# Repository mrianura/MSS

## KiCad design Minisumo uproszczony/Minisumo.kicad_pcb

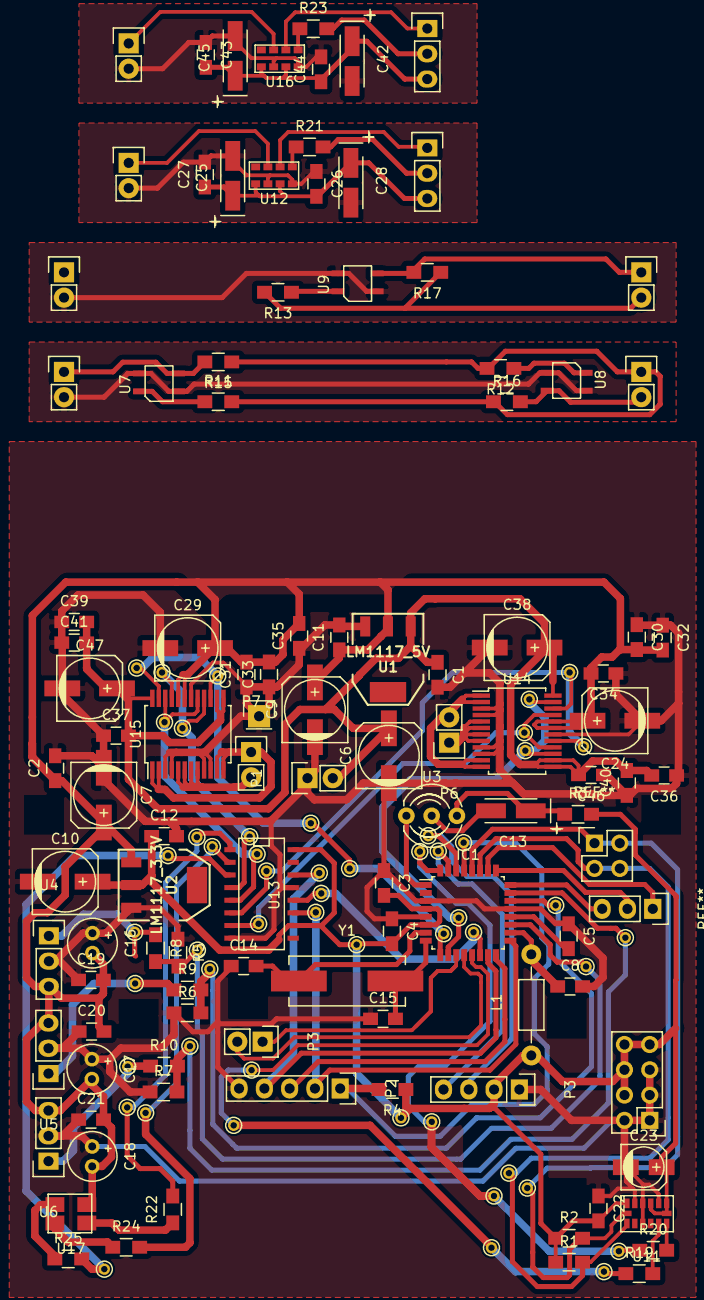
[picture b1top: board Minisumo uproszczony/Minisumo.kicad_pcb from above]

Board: 2 copper layers, 95 parts (0 on the bottom side), 56 nets.

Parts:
C1, C2, C3, C4, C5, C8, C11, C12, C19, C20, C21, C22, C26, C27, C30, C31, C32, C33, C34, C35, C36, C37, C39, C40, C41, C43, C44, C46: 100nF; C_0805_HandSoldering
C6, C7, C9, C10, C24, C29, C38, C47: 100uF; c_elec_6.3x7.7
C13, C25, C42: 4.7uF; TantalC_SizeA_EIA-3216_HandSoldering
C14, C15: 22pF; C_0805_HandSoldering
C16, C17, C18: 1uF; Elko_vert_11x5mm_RM2
C23: 22uF; c_elec_4x4.5
C28, C45: 1uF; TantalC_SizeA_EIA-3216_HandSoldering
IC1: ATMEGA328P-A; LQFP-32_7x7mm_Pitch0.8mm
L1: 100mH; Resistor_Horizontal_RM10mm
P1: bateria; Pin_Header_Straight_1x02
P2: PROGRAMATOR; Pin_Header_Straight_1x05
P3: CONN_01X04; Pin_Header_Straight_1x02
P3#2: CONN_01X04; Pin_Header_Straight_1x04
P6: silnik2; Pin_Header_Straight_1x02
P7: silnik1; Pin_Header_Straight_1x02
R1, R2, R4: 10K; R_0805_HandSoldering
R3: 330; R_0805_HandSoldering
R5, R6, R7: 22K; R_0805_HandSoldering
R8, R9, R10: 6K8; R_0805_HandSoldering
R11, R12, R13: 100; R_0805_HandSoldering
R15, R16, R17: 10k; R_0805_HandSoldering
R19, R20, R21, R23: 1k; R_0805_HandSoldering
R22, R24, R25: 220; R_0805_HandSoldering
U1: LM1117_5V; SOT223
U2: LM1117_3.3V; SOT223
U3: TSOP4838; LED-5MM-3
U4, U5, U6: SHARP_10-80; Pin_Header_Straight_1x03
U7, U8, U9: KTIR0711S
U11: MMA7455L; LGA_14
U12, U16: SFH7773; sfh7773
U13: 74HC595; SO-16-N
U14, U15: TB6612
U17: RGB_diode; RGB_C_Anode
Y1: 16mHz; Crystal_HC49-SD_SMD

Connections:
+3V3: C3.2, C4.2, C10.1, C12.1, C22.2, C23.1, C25.1, C26.2, C27.1, C28.1, C42.1, C43.2, C44.1, C45.1, IC1.4, IC1.6, L1.1, P3#2.2, R1.1, R2.1, R3.2, R4.1, R11.2, R12.2, R13.2, R15.1, R16.1, R17.1, U2.2, U11.1, U11.4, U11.6, U11.7, U12.1, U12.3, U13.10, U13.16, U16.1, U16.3
+5V: C2.1, C7.1, C9.1, C11.1, C16.2, C17.2, C18.2, C19.2, C20.2, C21.2, C24.1, C29.1, C30.2, C31.2, C32.2, C33.2, C34.2, C35.2, U1.2, U2.1, U4.3, U5.3, U6.3, U14.19, U14.20, U15.19, U15.20, U17.2
/ACC_DRDY: IC1.32, R20.1
/ACC_INT2: IC1.13, R19.1
/AIN_1: U13.5, U15.17, U15.22
/AIN_2: U13.4, U15.16, U15.21
/BIN_1: U13.6, U14.17, U14.22
/BIN_2: U13.7, U14.16, U14.21
/INT_10_1: IC1.12, P3.2, R23.2
/INT_10_2: IC1.11, P3.1, R21.2
/KILL: IC1.30, P3#2.3
/KTIR_(1): IC1.24, R15.2, U7.4
/KTIR_(2): IC1.25, R16.2, U8.4
/KTIR_(3): IC1.26, R17.2, U9.4
/MISO: IC1.16, P2.3
/MOSI: IC1.15, P2.4, U13.14
/PWM_A: IC1.9, U15.15, U15.23
/PWM_B: IC1.10, U14.15, U14.23
/RST_328: IC1.29, P2.1, R4.2
/SCK: IC1.17, P2.2, U13.11
/SCL: IC1.28, R2.2, U11.14, U12.6, U16.6
/SDA: IC1.27, R1.2, U11.13, U12.7, U16.7
/SHARP_1: IC1.19, R5.2, R8.2
/SHARP_2: IC1.22, R6.2, R9.2
/SHARP_3: IC1.23, R7.2, R10.2
/SS: IC1.14, U13.12
/START: IC1.31, P3#2.4
/S_A_1: P7.1, U15.1, U15.2, U15.11, U15.12
/S_A_2: P7.2, U15.5, U15.6, U15.7, U15.8
/S_B_1: P6.2, U14.1, U14.2, U14.11, U14.12
/S_B_2: P6.1, U14.5, U14.6, U14.7, U14.8
/XTAL1: C14.2, IC1.7, Y1.1
/XTAL2: C15.2, IC1.8, Y1.2
GND: C1.2, C2.2, C3.1, C4.1, C5.1, C6.2, C7.2, C8.2, C9.2, C10.2, C11.2, C12.2, C14.1, C15.1, C16.1, C17.1, C18.1, C19.1, C20.1, C21.1, C22.1, C23.2, C24.2, C25.2, C26.1, C27.2, C28.2, C29.2, C30.1, C31.1, C32.1, C33.1, C34.1, C35.1, C36.1, C37.1, C38.2, C39.1, C40.1, C41.1, C42.2, C43.1, C44.2, C45.2, C46.1, C47.2, IC1.3, IC1.5, IC1.21, P1.1, P2.5, P3#2.1, R5.1, R6.1, R7.1, U1.3, U2.3, U4.2, U5.2, U6.2, U7.2, U7.3, U8.2, U8.3, U9.2, U9.3, U11.2, U11.3, U11.5, U11.11, U12.2, U12.4, U13.8, U13.13, U14.3, U14.4, U14.9, U14.10, U14.18, U15.3, U15.4, U15.9, U15.10, U15.18, U16.2, U16.4
unnamed: C5.2, IC1.20
unnamed: C8.1, IC1.18, L1.2
unnamed: C13.1, R3.1, U3.3
unnamed: C13.2, U3.2
unnamed: IC1.1, U3.1
unnamed: R8.1, U4.1
unnamed: R9.1, U5.1
unnamed: R10.1, U6.1
unnamed: R11.1, U7.1
unnamed: R12.1, U8.1
unnamed: R13.1, U9.1
unnamed: R19.2, U11.9
unnamed: R20.2, U11.8
unnamed: R21.1, U12.5
unnamed: R22.1, U17.4
unnamed: R22.2, U13.1
unnamed: R23.1, U16.5
unnamed: R24.1, U17.3
unnamed: R24.2, U13.2
unnamed: R25.1, U17.1
unnamed: R25.2, U13.3
VCC: C1.1, C6.1, C36.2, C37.2, C38.1, C39.2, C40.2, C41.2, C46.2, C47.1, P1.2, U1.1, U14.13, U14.14, U14.24, U15.13, U15.14, U15.24

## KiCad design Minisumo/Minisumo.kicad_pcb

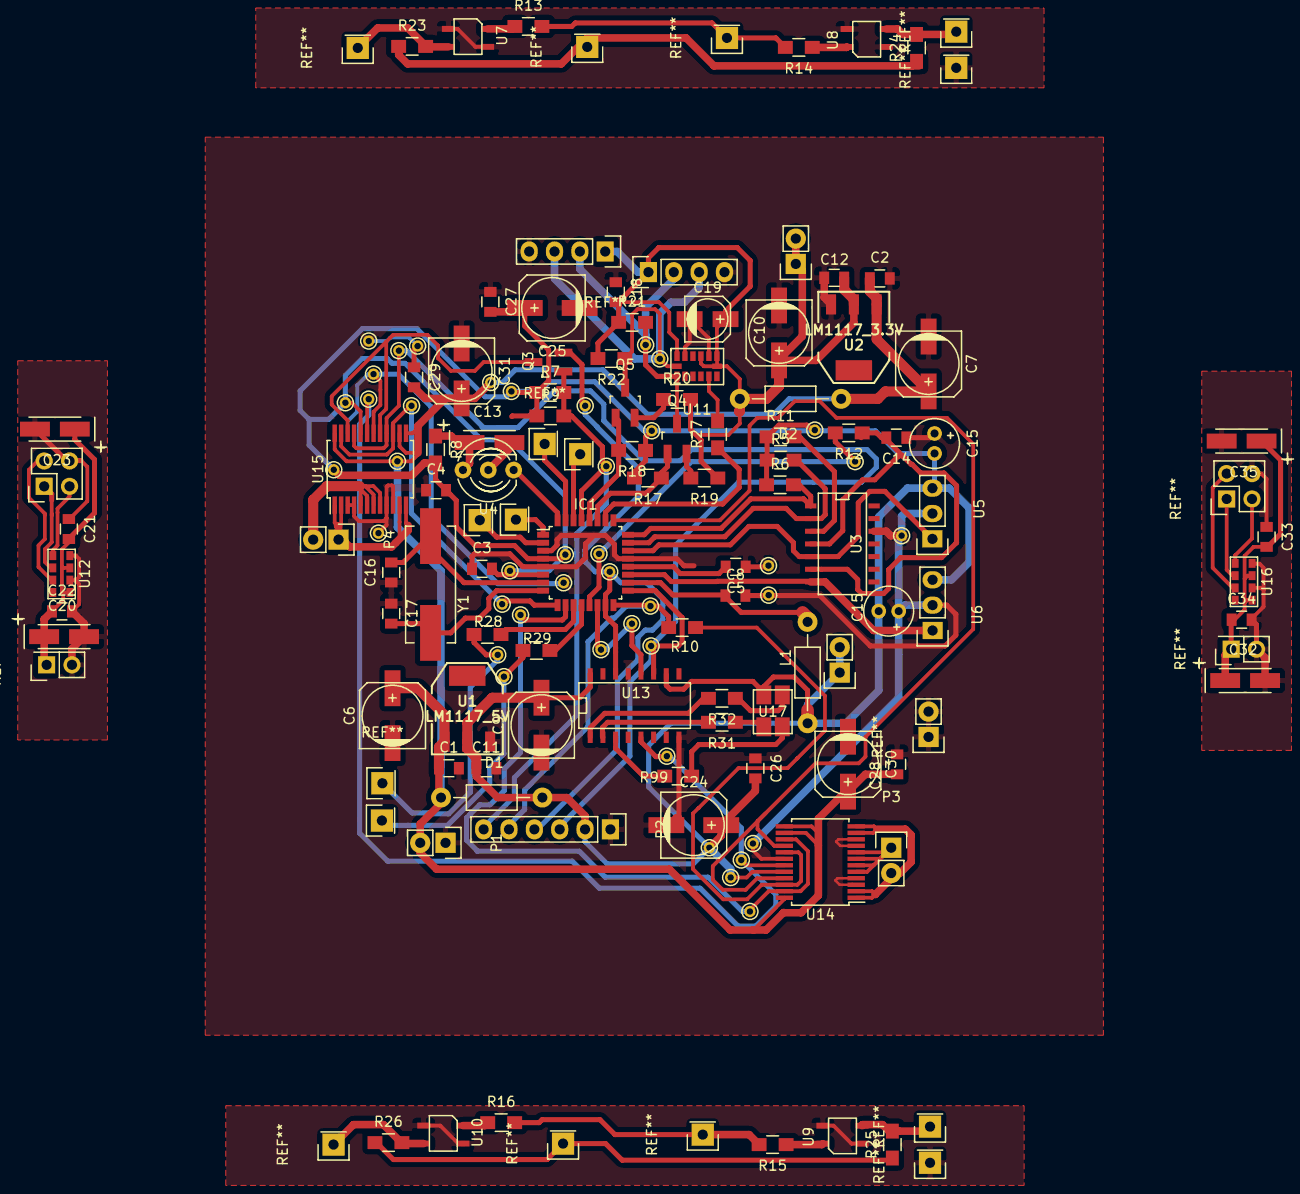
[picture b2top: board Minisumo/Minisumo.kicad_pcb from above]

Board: 2 copper layers, 93 parts (0 on the bottom side), 59 nets.

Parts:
C1, C2, C3, C4, C5, C8, C11, C12, C14, C18, C21, C22, C26, C27, C28, C29, C33, C34: 100nF; C_0805
C6, C7, C9, C10, C24, C25, C30, C31: 100uF; c_elec_6.3x7.7
C13, C20, C32: 4.7uF; TantalC_SizeA_EIA-3216_HandSoldering
C15, C15#2: 1uF; Elko_vert_11x5mm_RM2
C16, C17: 22pF; C_0805
C19: 22uF; c_elec_4x4.5
C23, C35: 1uF; TantalC_SizeA_EIA-3216_HandSoldering
D1, D2: D_Schottky; Resistor_Horizontal_RM10mm
IC1: ATMEGA328P-A; LQFP-32_7x7mm_Pitch0.8mm
L1: 100mH; Resistor_Horizontal_RM10mm
P1: bateria; Pin_Header_Straight_1x02
P2: PROGRAMATOR; Pin_Header_Straight_1x06
P3: silnik2; Pin_Header_Straight_1x02
P4: silnik1; Pin_Header_Straight_1x02
Q3: BC817-25; SOT-23_Handsoldering
Q4, Q5: BSS138; SOT-23_Handsoldering
R5, R6: 47k; R_0805_HandSoldering
R7, R10, R23, R24, R25, R26: 10k; R_0805_HandSoldering
R8: 330; R_0805_HandSoldering
R9: 10K; R_0805_HandSoldering
R11: 3k; R_0805_HandSoldering
R12: 33k; R_0805_HandSoldering
R13, R14, R15, R16: 100; R_0805_HandSoldering
R17, R18, R19, R20, R21, R22: 4,7k; R_0805_HandSoldering
R27, R28, R29: 1k; R_0805_HandSoldering
R31, R32, R99: 220; R_0805_HandSoldering
U1: LM1117_5V; SOT223
U2: LM1117_3.3V; SOT223
U3: LM339; SOIC-14_N
U4: IR; LED-5MM-3
U5: Socket_Strip_Straight_1x03
U6: SHARP_10-80; Socket_Strip_Straight_1x03
U7, U8, U9, U10: KTIR0711S
U11: MMA7455L; LGA_14
U12, U16: SFH7773; sfh7773
U13: 74HC595; SO-16-N
U14, U15: TB6612
U17: RGB; RGB_C_Anode
Y1: 16mHz; Crystal_HC49-SD_SMD

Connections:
+3V3: C10.1, C12.1, C18.2, C19.1, C20.1, C21.2, C22.1, C23.1, C32.1, C33.2, C34.1, C35.1, D2.2, R13.2, R14.2, R15.2, R16.2, R19.1, R20.2, R21.1, R22.2, U2.2, U11.1, U11.4, U11.6, U11.7, U12.1, U12.3, U16.1, U16.3
+5V: C3.2, C4.2, C9.1, C11.1, C15.2, C15#2.2, C24.1, C25.1, C26.2, C27.2, D1.2, IC1.4, IC1.6, L1.1, P2.2, R5.1, R6.1, R7.1, R8.2, R9.1, R11.1, R17.2, R18.1, R23.1, R24.1, R25.1, R26.1, U1.2, U5.3, U6.3, U13.10, U13.16, U14.20, U15.20, U17.2
/ACC_INT2: IC1.26, R27.1
/AIN_1: Q3.3, U15.17, U15.22
/AIN_2: IC1.17, P2.3, U13.11, U15.16, U15.21
/BIN_1: R10.1, U14.17, U14.22
/BIN_2: IC1.25, U14.16, U14.21
/INT_10_1: IC1.12, R29.2
/INT_10_2: IC1.11, R28.2
/MISO_328: IC1.16, P2.5, R10.2
/MOSI_328: IC1.15, P2.4, Q3.2, U13.14
/PCINT16_(1): IC1.30, R23.2, U7.4
/PCINT17_(2): IC1.31, R24.2, U8.4
/PCINT20_(3): IC1.2, R25.2, U9.4
/PCINT21_(4): IC1.1, R26.2, U10.4
/PWM_A: IC1.9, U15.15, U15.23
/PWM_B: IC1.10, U14.15, U14.23
/PWM_SHARP: IC1.13, R12.2
/RST_328: IC1.29, P2.6, Q3.1, R7.2, R9.2
/SCL: IC1.28, Q5.1, R18.2
/SCL_3.3: Q5.3, R22.1, U11.14, U12.6, U16.6
/SDA: IC1.27, Q4.1, R17.1
/SDA_3.3: Q4.3, R21.2, U11.13, U12.7, U16.7
/SHARP1_INT: IC1.24, R6.2, U3.1
/SHARP2_INT: IC1.23, R5.2, U3.2
/SHARP_1: IC1.19, U3.7, U6.1
/SHARP_2: IC1.22, U3.5, U5.1
/SHARP_POZ: C14.2, R12.1, U3.4, U3.6
/STBY_ON: U13.5, U14.19, U15.19
/S_A_1: P4.1, U15.1, U15.2, U15.11, U15.12
/S_A_2: P4.2, U15.5, U15.6, U15.7, U15.8
/S_B_1: P3.2, U14.1, U14.2, U14.11, U14.12
/S_B_2: P3.1, U14.5, U14.6, U14.7, U14.8
/XTAL1: C16.2, IC1.7, Y1.1
/XTAL2: C17.2, IC1.8, Y1.2
GND: C1.2, C2.2, C3.1, C4.1, C5.1, C6.2, C7.2, C8.2, C9.2, C10.2, C11.2, C12.2, C14.1, C15.1, C15#2.1, C16.1, C17.1, C18.1, C19.2, C20.2, C21.1, C22.2, C23.2, C24.2, C25.2, C26.1, C27.1, C28.1, C29.1, C30.2, C31.2, C32.2, C33.1, C34.2, C35.2, IC1.3, IC1.5, IC1.21, P1.1, P2.1, U1.3, U2.3, U3.12, U5.2, U6.2, U7.2, U7.3, U8.2, U8.3, U9.2, U9.3, U10.2, U10.3, U11.2, U11.5, U12.2, U12.4, U13.8, U13.13, U14.3, U14.4, U14.9, U14.10, U14.18, U15.3, U15.4, U15.9, U15.10, U15.18, U16.2, U16.4
unnamed: C5.2, IC1.20
unnamed: C8.1, IC1.18, L1.2
unnamed: C13.1, R8.1, U4.3
unnamed: C13.2, U4.2
unnamed: IC1.14, U13.12
unnamed: IC1.32, U4.1
unnamed: Q4.2, R19.2
unnamed: Q5.2, R20.1
unnamed: R11.2, U3.3
unnamed: R13.1, U7.1
unnamed: R14.1, U8.1
unnamed: R15.1, U9.1
unnamed: R16.1, U10.1
unnamed: R27.2, U11.9
unnamed: R28.1, U12.5
unnamed: R29.1, U16.5
unnamed: R31.1, U17.1
unnamed: R31.2, U13.2
unnamed: R32.1, U17.4
unnamed: R32.2, U13.1
unnamed: R99.1, U17.3
unnamed: R99.2, U13.3
VCC: C1.1, C2.1, C6.1, C7.1, C28.2, C29.2, C30.1, C31.1, D1.1, D2.1, P1.2, U1.1, U2.1, U14.13, U14.14, U14.24, U15.13, U15.14, U15.24

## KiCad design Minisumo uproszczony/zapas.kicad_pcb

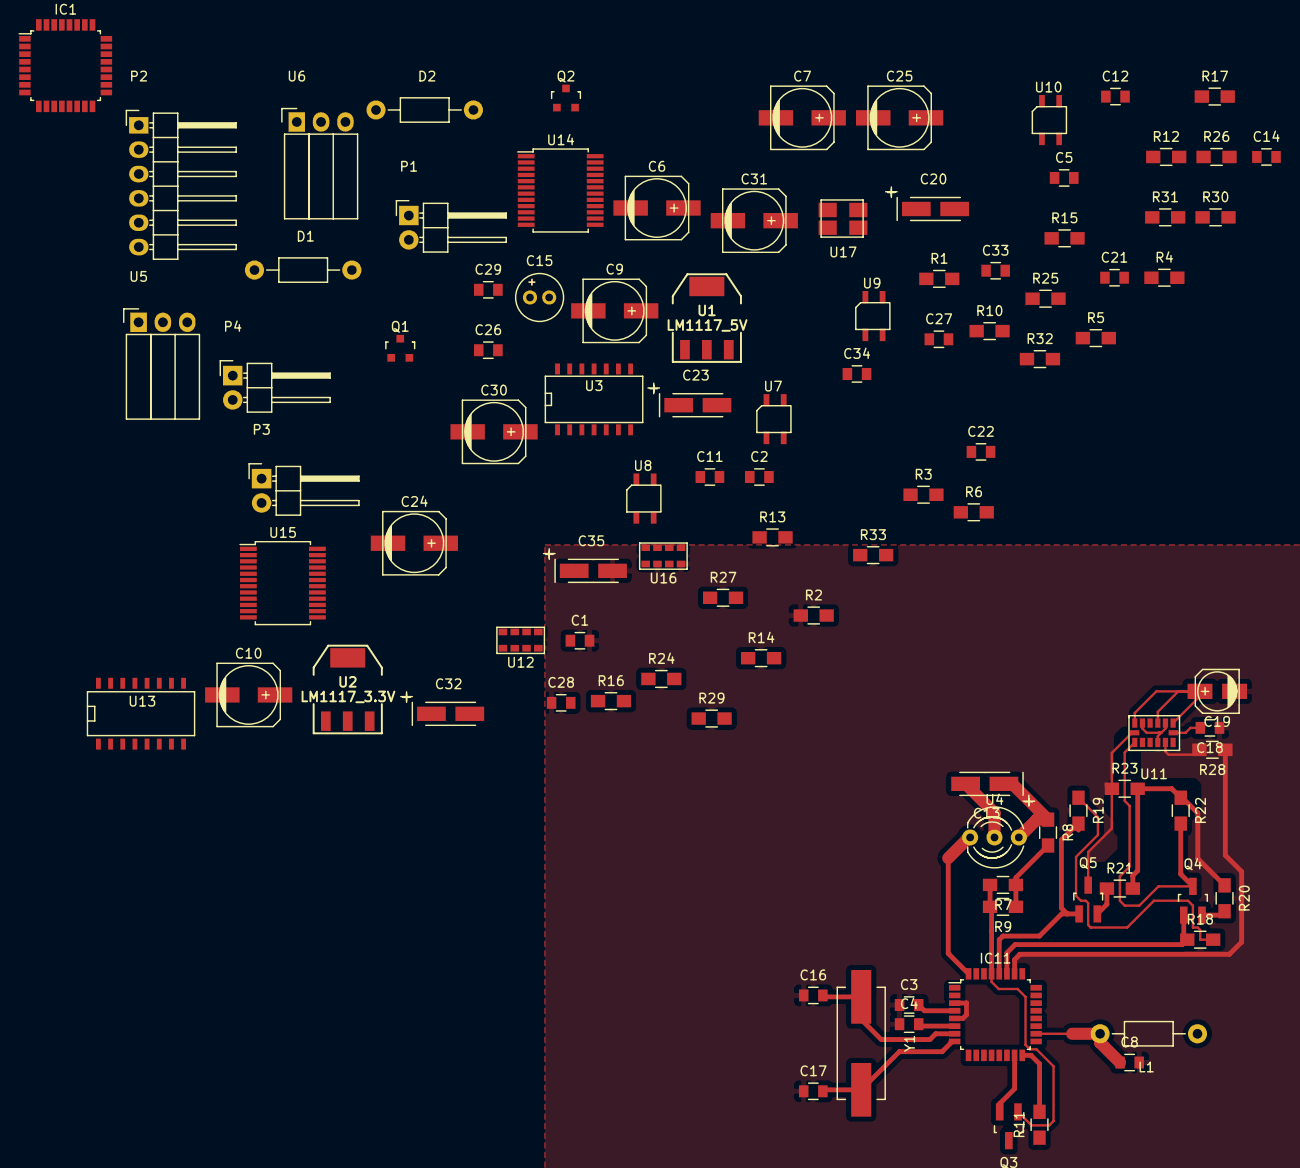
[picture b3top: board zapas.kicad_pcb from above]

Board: 2 copper layers, 100 parts (0 on the bottom side), 64 nets.

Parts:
C1, C2, C3, C4, C5, C8, C11, C12, C14, C18, C21, C22, C26, C27, C28, C29, C33, C34: 100nF; C_0805
C6, C7, C9, C10, C24, C25, C30, C31: 100uF; c_elec_6.3x7.7
C13, C20, C32: 4.7uF; TantalC_SizeA_EIA-3216_HandSoldering
C15: 1uF; Elko_vert_11x5mm_RM2
C16, C17: 22pF; C_0805
C19: 22uF; c_elec_4x4.5
C23, C35: 1uF; TantalC_SizeA_EIA-3216_HandSoldering
D1, D2: D_Schottky; Resistor_Horizontal_RM10mm
IC1, IC11: ATMEGA328P-A; LQFP-32_7x7mm_Pitch0.8mm
L1: 100mH; Resistor_Horizontal_RM10mm
P1: bateria; Pin_Header_Angled_1x02
P2: PROGRAMATOR; Pin_Header_Angled_1x06
P3: silnik2; Pin_Header_Angled_1x02
P4: silnik1; Pin_Header_Angled_1x02
Q1, Q2: IRLML2246TRPBF; SOT-23
Q3: BC817-25; SOT-23_Handsoldering
Q4, Q5: BSS138; SOT-23_Handsoldering
R1, R2, R5, R6: 47k; R_0805_HandSoldering
R3, R4, R28, R29, R30: 1k; R_0805_HandSoldering
R7, R11, R24, R25, R26, R27: 10k; R_0805_HandSoldering
R8: 330; R_0805_HandSoldering
R9: 10K; R_0805_HandSoldering
R10, R12: 3k; R_0805_HandSoldering
R13: 33k; R_0805_HandSoldering
R14, R15, R16, R17: 100; R_0805_HandSoldering
R18, R19, R20, R21, R22, R23: 4,7k; R_0805_HandSoldering
R31, R32, R33: 220; R_0805_HandSoldering
U1: LM1117_5V; SOT223
U2: LM1117_3.3V; SOT223
U3: LM339; SOIC-14_N
U4: TSOP4836; LED-5MM-3
U5, U6: SHARP_10-80; Socket_Strip_Angled_1x03
U7, U8, U9, U10: KTIR0711S
U11: MMA7455L; LGA_14
U12, U16: SFH7773; sfh7773
U13: 74HC595; SO-16-N
U14, U15: TB6612
U17: RGB_diode; RGB_C_Anode
Y1: 16mHz; Crystal_HC49-SD_SMD

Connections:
+3V3: C18.2, C19.1, C20.1, C21.2, C22.1, C23.1, C32.1, C33.2, C34.1, C35.1, Q2.2, R14.2, R15.2, R16.2, R17.2, R20.1, R21.2, R22.1, R23.2, U11.1, U11.4, U11.6, U11.7, U12.1, U12.3, U16.1, U16.3
+5V: C15.2, C24.1, C25.1, C26.2, C27.2, Q1.2, R5.1, R6.1, R10.1, R12.1, R18.2, R19.1, R24.1, R25.1, R26.1, R27.1, U5.3, U6.3, U14.20, U15.20
+5VA: C3.2, C4.2, C9.1, C11.1, D1.2, IC1.4, IC1.6, IC11.4, IC11.6, L1.1, P2.6, Q1.3, R7.1, R8.2, R9.1, U1.2, U13.10, U17.2
/ACC_INT2: IC1.26, IC11.26, R28.1
/AIN_1: Q3.3, U15.17, U15.22
/AIN_2: IC1.17, IC11.17, P2.3, U13.11, U15.16, U15.21
/BIN_1: R11.1, U14.17, U14.22
/BIN_2: IC1.25, IC11.25, U14.16, U14.21
/INT_10_1: IC1.12, IC11.12, R30.2
/INT_10_2: IC1.1, IC11.1, R29.2
/MISO_328: IC1.16, IC11.16, P2.1, R11.2
/MOSI_328: IC1.15, IC11.15, P2.2, Q3.2, U13.14
/PCINT16_(1): IC1.30, IC11.30, R24.2, U7.4
/PCINT17_(2): IC1.31, IC11.31, R25.2, U8.4
/PCINT20_(3): IC1.2, IC11.2, R26.2, U9.4
/PCINT21_(4): IC1.11, IC11.11, R27.2, U10.4
/PWM_A: IC1.9, IC11.9, U15.15, U15.23
/PWM_B: IC1.10, IC11.10, U14.15, U14.23
/PWM_SHARP: IC1.13, IC11.13, R13.2
/RST_328: IC1.29, IC11.29, P2.4, Q3.1, R7.2, R9.2
/SCL: IC1.28, IC11.28, Q5.1, R19.2
/SCL_3.3: Q5.3, R23.1, U11.14, U12.6, U16.6
/SDA: IC1.27, IC11.27, Q4.1, R18.1
/SDA_3.3: Q4.3, R22.2, U11.13, U12.7, U16.7
/SHARP1_INT: IC1.23, IC11.23, R6.2, U3.1
/SHARP2_INT: IC1.24, IC11.24, R5.2, U3.2
/SHARP_1: IC1.19, IC11.19, U3.7, U6.1
/SHARP_2: IC1.22, IC11.22, U3.5, U5.1
/SHARP_POZ: C14.2, R13.1, U3.4, U3.6
/SS_328: IC1.14, IC11.14, U13.12
/STBY_ON: U13.5, U14.19, U15.19
/S_A_1: P4.1, U15.1, U15.2, U15.11, U15.12
/S_A_2: P4.2, U15.5, U15.6, U15.7, U15.8
/S_B_1: P3.1, U14.1, U14.2, U14.11, U14.12
/S_B_2: P3.2, U14.5, U14.6, U14.7, U14.8
/XTAL1: C16.2, IC1.7, IC11.7, Y1.1
/XTAL2: C17.2, IC1.8, IC11.8, Y1.2
/ZAS_ON: R3.1, R4.1, U13.4
GND: C1.2, C2.2, C3.1, C4.1, C5.1, C6.2, C7.2, C8.2, C9.2, C10.2, C11.2, C12.2, C14.1, C15.1, C16.1, C17.1, C18.1, C19.2, C20.2, C21.1, C22.2, C23.2, C24.2, C25.2, C26.1, C27.1, C28.1, C29.1, C30.2, C31.2, C32.2, C33.1, C34.2, C35.2, IC1.3, IC1.5, IC1.21, IC11.3, IC11.5, IC11.21, P1.2, P2.5, R1.2, R2.1, U1.3, U2.3, U3.12, U5.2, U6.2, U7.2, U7.3, U8.2, U8.3, U9.2, U9.3, U10.2, U10.3, U11.2, U11.5, U11.10, U12.2, U12.4, U13.8, U13.13, U14.3, U14.4, U14.9, U14.10, U14.18, U15.3, U15.4, U15.9, U15.10, U15.18, U16.2, U16.4
unnamed: C5.2, IC1.20, IC11.20
unnamed: C8.1, IC1.18, IC11.18, L1.2
unnamed: C10.1, C12.1, D2.2, Q2.3, U2.2
unnamed: C13.1, R8.1, U4.3
unnamed: C13.2, U4.2
unnamed: IC1.32, IC11.32, U4.1
unnamed: Q1.1, R1.1, R3.2
unnamed: Q2.1, R2.2, R4.2
unnamed: Q4.2, R20.2
unnamed: Q5.2, R21.1
unnamed: R12.2, U3.3
unnamed: R14.1, U7.1
unnamed: R15.1, U8.1
unnamed: R16.1, U9.1
unnamed: R17.1, U10.1
unnamed: R28.2, U11.9
unnamed: R29.1, U12.5
unnamed: R30.1, U16.5
unnamed: R31.1, U17.1
unnamed: R31.2, U13.1
unnamed: R32.1, U17.3
unnamed: R32.2, U13.2
unnamed: R33.1, U17.4
unnamed: R33.2, U13.3
VCC: C1.1, C2.1, C6.1, C7.1, C28.2, C29.2, C30.1, C31.1, D1.1, D2.1, P1.1, U1.1, U2.1, U13.16, U14.13, U14.14, U14.24, U15.13, U15.14, U15.24

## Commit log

2015-11-12 :boom::camel: Added .gitattributes
2015-11-12 sad
    asd
2015-11-12 UPDATE 1
    UPDATE 1
2015-11-13 poprawa schematu
    nieznaczna poprawa schematu 13
2015-11-13 Model3D
    poprawienie modelu 3D
2015-11-15 Bez komparatorow
    uproszczono schemat
2015-11-16 3 Sharpy
    dodano sharpa, dodano 2 attiny
2015-11-16 poprawa modelu
    poprawa modelu, nowy sharp
2015-11-16 3 KTIRY
    uproszczenie schematu, usunięcie 1 czujnika odległości, usunięcie 2
    ATtiny13
2015-11-16 .
    .
2015-11-17 SCHEMAT
    PCB
2015-11-17 PCB
    PCB
2015-11-22 poprawione PCB
    PCB v2
2015-11-24 PCB v3
    PCB v3
